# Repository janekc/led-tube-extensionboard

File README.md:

# led-tube
PCB design for a portable, battery powered, tube shaped partylight.

It should run with 4 x 18650 lithium battery cells, that can be recharged through USB Power Delivery 3.0 with up to 18W. This would be achived using the IP5328P IC reference desing to handle charging and discharging of the 4 parallel cells.

The IP5328P can output uo to 5v 3.1A which, according to [Quins' real world LED Power consumption sheet](https://quinled.info/2020/03/12/digital-led-power-usage/), would be enough to power around 70 WS2812b 5050 RGB LEDs.

#### Extra Parts that you will need to buy if you want to build your own tube

- [Acrylic PLEXIGLASS Tubes 50/44mm](https://hbholzmaus.de/epages/Store7_Shop34800.sf/de_DE/?ObjectPath=/Shops/Shop34800/Categories/Rohre/%22Rohre%20satiniert%22)

- [QuinLED-ESP32-ABE Ethernet ESP32 Board](https://quinled.info/quinled-esp32/)

- [18650 lithium batteries](https://www.akkushop.de/de/3400mah-panasonic-18650-li-ion-akku-mit-eigener-schutzschaltung-ca.-69-x-1861mm-beachten/)

#### Projects that have been used as Inspiration

- https://github.com/YC-Lammy/IP5328P-powerbank_design

- https://hackaday.io/project/177748-modular-18650-power-bank

- https://www.flux.ai/jecstronic/powerbank-board

- https://github.com/janekc/diodeplate

- https://github.com/mstuij/QuinLED-ESP32-Breakout

- https://quinled.info/quinled-esp32-kicad-files/

#### Useful datasheets

- http://www.injoinic.com/wwwroot/uploads/files/20200221/ec29931791194a51119ee1d6a4a21efb.pdf

#### Links (not related directly)

- https://github.com/kkr0kk/PowerBank-DIY

- https://kicadrookie.blogspot.com/2022/07/kicad-projects-powerbank-pcb-IP5328P%20.html

- https://www.lcsc.com/search?q=IP5328P

- https://www.reddit.com/r/batteries/comments/onzm58/how_to_get_12v_for_a_amplifier_with_a_ip5328p/

- https://www.ti.com/lit/ug/tiduey1a/tiduey1a.pdf?ts=1696105000442

- https://hackaday.io/project/184947-pi-cm4-carrier-io-board

- https://www.aliexpress.com/item/33057941535.html?aff_fcid=06bf9dcd74484ab2a2f4b222b06f5361-1696411999482-09499-_AgWfRQ&aff_fsk=_AgWfRQ&aff_platform=shareComponent-detail&aff_trace_key=06bf9dcd74484ab2a2f4b222b06f5361-1696411999482-09499-_AgWfRQ&afSmartRedirect=y

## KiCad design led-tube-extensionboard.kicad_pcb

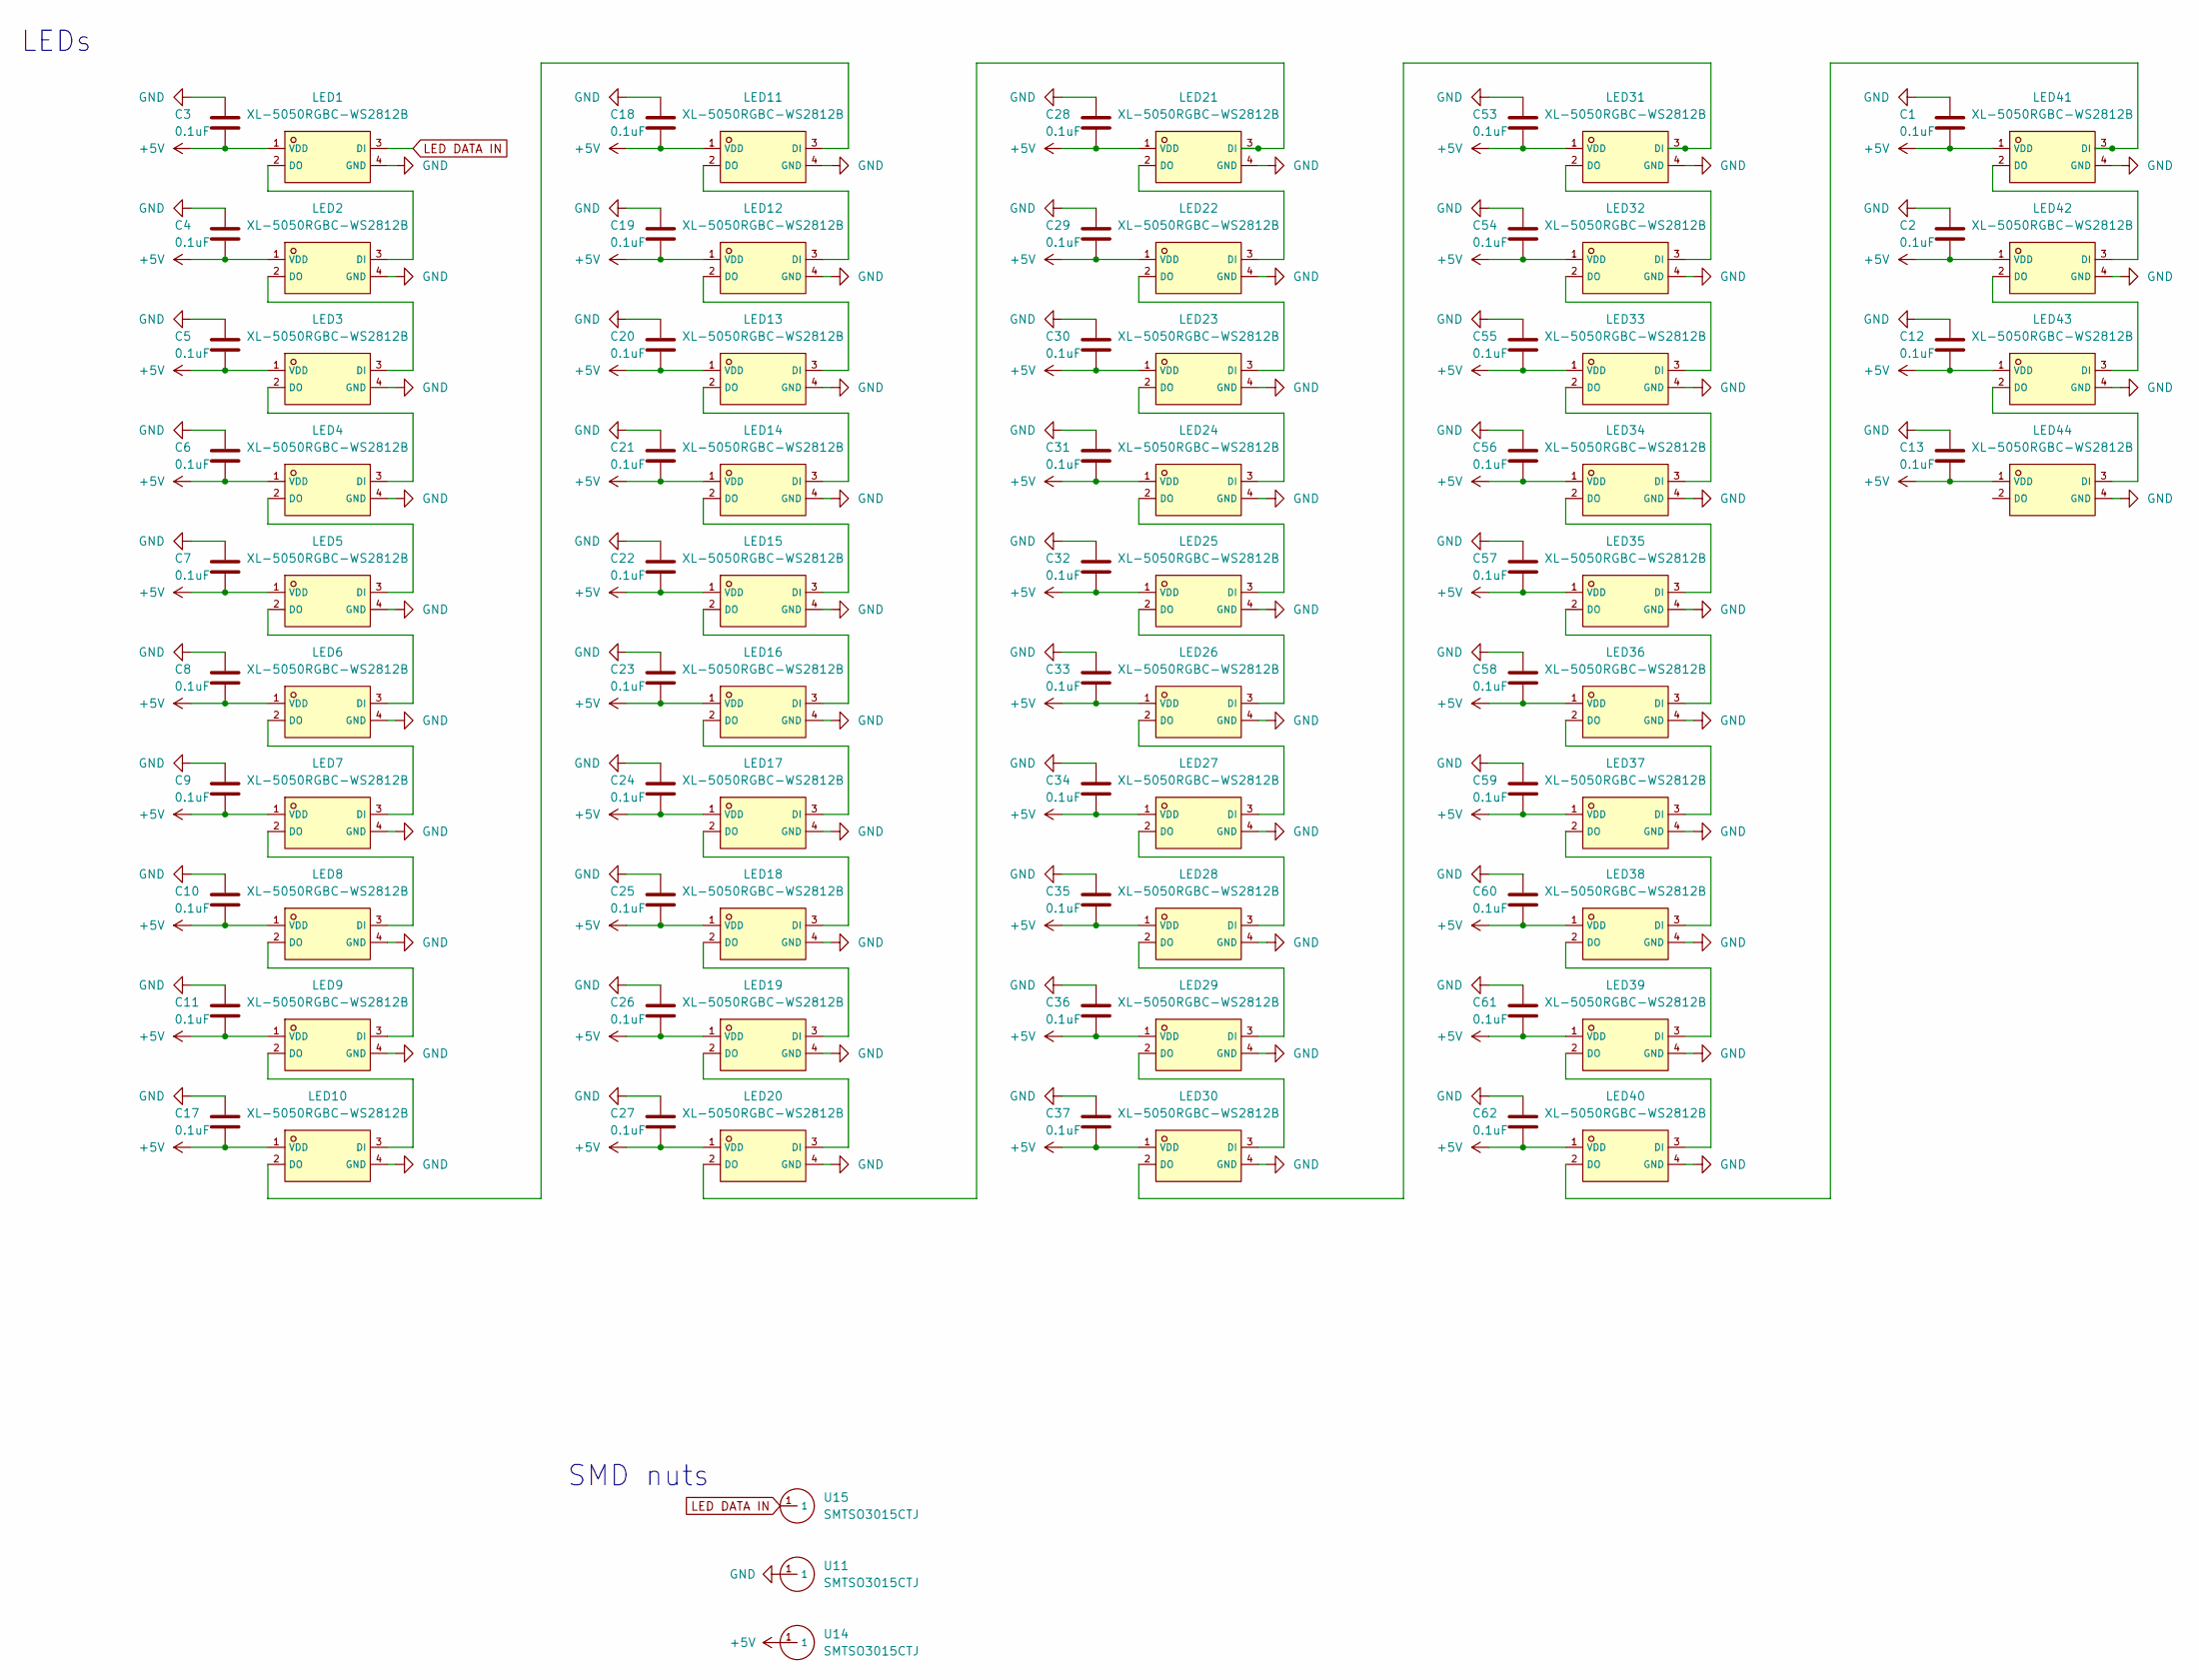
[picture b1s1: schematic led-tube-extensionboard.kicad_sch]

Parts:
C1, C2, C3, C4, C5, C6, C7, C8, C9, C10, C11, C12, C13, C17, C18, C19, C20, C21, C22, C23, C24, C25, C26, C27, C28, C29, C30, C31, C32, C33, C34, C35, C36, C37, C53, C54, C55, C56, C57, C58, C59, C60, C61, C62: 0.1uF; C_0603_1608Metric_Pad1.08x0.95mm_HandSolder
LED1, LED2, LED3, LED4, LED5, LED6, LED7, LED8, LED9, LED10, LED11, LED12, LED13, LED14, LED15, LED16, LED17, LED18, LED19, LED20, LED21, LED22, LED23, LED24, LED25, LED26, LED27, LED28, LED29, LED30, LED31, LED32, LED33, LED34, LED35, LED36, LED37, LED38, LED39, LED40, LED41, LED42, LED43, LED44: XL-5050RGBC-WS2812B; LED_WS2812B_PLCC4_5.0x5.0mm_P3.2mm; LCSC # C2843785
U11, U14, U15: SMTSO3015CTJ; SMTSO3030CTJ; LCSC # C2915308

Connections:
+5V: C1.2, C2.2, C3.2, C4.2, C5.2, C6.2, C7.2, C8.2, C9.2, C10.2, C11.2, C12.2, C13.2, C17.2, C18.2, C19.2, C20.2, C21.2, C22.2, C23.2, C24.2, C25.2, C26.2, C27.2, C28.2, C29.2, C30.2, C31.2, C32.2, C33.2, C34.2, C35.2, C36.2, C37.2, C53.2, C54.2, C55.2, C56.2, C57.2, C58.2, C59.2, C60.2, C61.2, C62.2, LED1.1 (VDD), LED2.1 (VDD), LED3.1 (VDD), LED4.1 (VDD), LED5.1 (VDD), LED6.1 (VDD), LED7.1 (VDD), LED8.1 (VDD), LED9.1 (VDD), LED10.1 (VDD), LED11.1 (VDD), LED12.1 (VDD), LED13.1 (VDD), LED14.1 (VDD), LED15.1 (VDD), LED16.1 (VDD), LED17.1 (VDD), LED18.1 (VDD), LED19.1 (VDD), LED20.1 (VDD), LED21.1 (VDD), LED22.1 (VDD), LED23.1 (VDD), LED24.1 (VDD), LED25.1 (VDD), LED26.1 (VDD), LED27.1 (VDD), LED28.1 (VDD), LED29.1 (VDD), LED30.1 (VDD), LED31.1 (VDD), LED32.1 (VDD), LED33.1 (VDD), LED34.1 (VDD), LED35.1 (VDD), LED36.1 (VDD), LED37.1 (VDD), LED38.1 (VDD), LED39.1 (VDD), LED40.1 (VDD), LED41.1 (VDD), LED42.1 (VDD), LED43.1 (VDD), LED44.1 (VDD), U14.1
GND: C1.1, C2.1, C3.1, C4.1, C5.1, C6.1, C7.1, C8.1, C9.1, C10.1, C11.1, C12.1, C13.1, C17.1, C18.1, C19.1, C20.1, C21.1, C22.1, C23.1, C24.1, C25.1, C26.1, C27.1, C28.1, C29.1, C30.1, C31.1, C32.1, C33.1, C34.1, C35.1, C36.1, C37.1, C53.1, C54.1, C55.1, C56.1, C57.1, C58.1, C59.1, C60.1, C61.1, C62.1, LED1.4 (GND), LED2.4 (GND), LED3.4 (GND), LED4.4 (GND), LED5.4 (GND), LED6.4 (GND), LED7.4 (GND), LED8.4 (GND), LED9.4 (GND), LED10.4 (GND), LED11.4 (GND), LED12.4 (GND), LED13.4 (GND), LED14.4 (GND), LED15.4 (GND), LED16.4 (GND), LED17.4 (GND), LED18.4 (GND), LED19.4 (GND), LED20.4 (GND), LED21.4 (GND), LED22.4 (GND), LED23.4 (GND), LED24.4 (GND), LED25.4 (GND), LED26.4 (GND), LED27.4 (GND), LED28.4 (GND), LED29.4 (GND), LED30.4 (GND), LED31.4 (GND), LED32.4 (GND), LED33.4 (GND), LED34.4 (GND), LED35.4 (GND), LED36.4 (GND), LED37.4 (GND), LED38.4 (GND), LED39.4 (GND), LED40.4 (GND), LED41.4 (GND), LED42.4 (GND), LED43.4 (GND), LED44.4 (GND), U11.1
LED DATA IN: LED1.3 (DI), U15.1
unnamed: LED1.2 (DO), LED2.3 (DI)
unnamed: LED2.2 (DO), LED3.3 (DI)
unnamed: LED3.2 (DO), LED4.3 (DI)
unnamed: LED4.2 (DO), LED5.3 (DI)
unnamed: LED5.2 (DO), LED6.3 (DI)
unnamed: LED6.2 (DO), LED7.3 (DI)
unnamed: LED7.2 (DO), LED8.3 (DI)
unnamed: LED8.2 (DO), LED9.3 (DI)
unnamed: LED9.2 (DO), LED10.3 (DI)
unnamed: LED10.2 (DO), LED11.3 (DI)
unnamed: LED11.2 (DO), LED12.3 (DI)
unnamed: LED12.2 (DO), LED13.3 (DI)
unnamed: LED13.2 (DO), LED14.3 (DI)
unnamed: LED14.2 (DO), LED15.3 (DI)
unnamed: LED15.2 (DO), LED16.3 (DI)
unnamed: LED16.2 (DO), LED17.3 (DI)
unnamed: LED17.2 (DO), LED18.3 (DI)
unnamed: LED18.2 (DO), LED19.3 (DI)
unnamed: LED19.2 (DO), LED20.3 (DI)
unnamed: LED20.2 (DO), LED21.3 (DI)
unnamed: LED21.2 (DO), LED22.3 (DI)
unnamed: LED22.2 (DO), LED23.3 (DI)
unnamed: LED23.2 (DO), LED24.3 (DI)
unnamed: LED24.2 (DO), LED25.3 (DI)
unnamed: LED25.2 (DO), LED26.3 (DI)
unnamed: LED26.2 (DO), LED27.3 (DI)
unnamed: LED27.2 (DO), LED28.3 (DI)
unnamed: LED28.2 (DO), LED29.3 (DI)
unnamed: LED29.2 (DO), LED30.3 (DI)
unnamed: LED30.2 (DO), LED31.3 (DI)
unnamed: LED31.2 (DO), LED32.3 (DI)
unnamed: LED32.2 (DO), LED33.3 (DI)
unnamed: LED33.2 (DO), LED34.3 (DI)
unnamed: LED34.2 (DO), LED35.3 (DI)
unnamed: LED35.2 (DO), LED36.3 (DI)
unnamed: LED36.2 (DO), LED37.3 (DI)
unnamed: LED37.2 (DO), LED38.3 (DI)
unnamed: LED38.2 (DO), LED39.3 (DI)
unnamed: LED39.2 (DO), LED40.3 (DI)
unnamed: LED40.2 (DO), LED41.3 (DI)
unnamed: LED41.2 (DO), LED42.3 (DI)
unnamed: LED42.2 (DO), LED43.3 (DI)
unnamed: LED43.2 (DO), LED44.3 (DI)

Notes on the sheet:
SMD nuts
LEDs

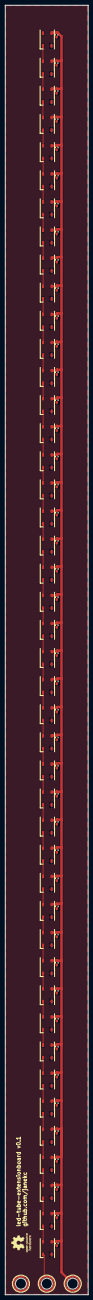
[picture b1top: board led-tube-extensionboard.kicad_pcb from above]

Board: 2 copper layers, 32.0 x 498.0 mm, 91 parts (0 on the bottom side), 46 nets.

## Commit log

2023-10-04 clone from led-tube
2023-10-15 regenrate gerber files, add tags
